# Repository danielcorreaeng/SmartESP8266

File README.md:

# SmartESP8266

Project for residential automation for ESP8266 NodeMcu board using arduino IDE with IR controller, MQTT and command line based HTTP request.

## Final note

I concluded that the best model is to use infrared with http and use a third program to manage the rest. 
In my case, I used the homeassistant (https://home-assistant.io/) and returned to the IR-Blaster model (https://github.com/mdhiggins/ESP8266-HTTP-IR-Blaster)

## Bases

https://github.com/mdhiggins/ESP8266-HTTP-IR-Blaster

https://github.com/tzapu/WiFiManager

https://www.filipeflop.com/blog/controle-monitoramento-iot-nodemcu-e-mqtt/

https://www.hackster.io/BuddyC/wifi-ir-blaster-af6bca

http://knolleary.net

## Contributors

See also the list of [contributors](contributors.md) who participated in this project.

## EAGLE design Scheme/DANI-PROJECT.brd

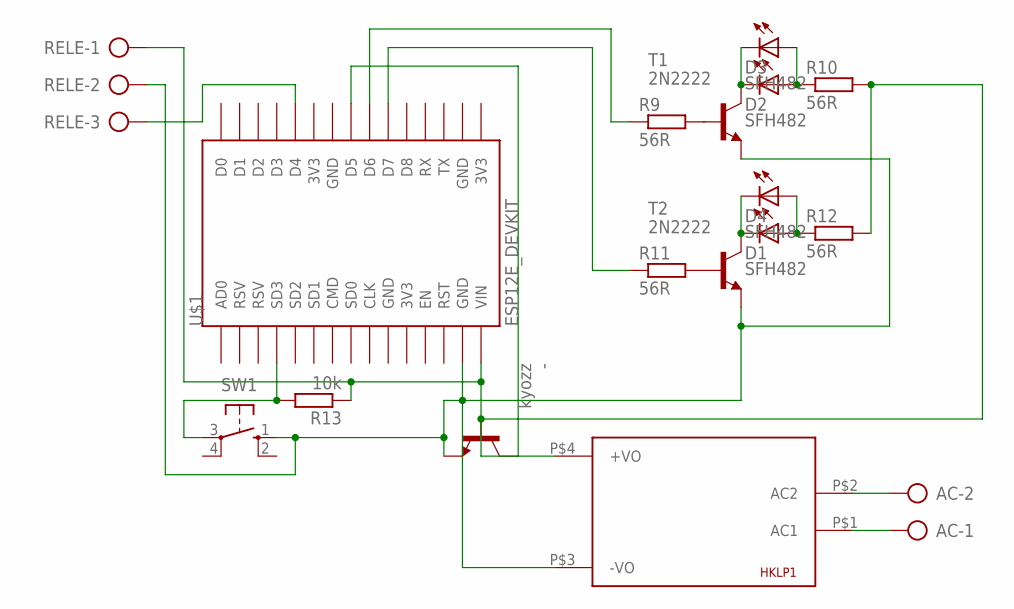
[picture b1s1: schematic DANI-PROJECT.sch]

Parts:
-: kyozz; TO92-EBC
AC: AK500/2-H
D1, D2, D3, D4: SFH482
HKLP1: HKLPM01
R9, R10, R11, R12: 56R; 0207/7
R13: 10k; 0207/7
RELE: AK500/3-H
SW1: 10-XX; B3F-10XX
T1, T2: 2N2222; TO18
U$1: ESP12E_DEVKIT

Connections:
unnamed: AC.2, HKLP1.P$2 (AC2)
unnamed: AC.1, HKLP1.P$1 (AC1)
unnamed: R13.2, SW1.3, U$1.SD3
unnamed: D1.K (C), D4.K (C), T2.3 (C)
unnamed: R11.2, T2.2 (B)
unnamed: R9.2, T1.2 (B)
unnamed: D2.A, D3.A, R10.1
unnamed: D2.K (C), D3.K (C), T1.3 (C)
unnamed: -.B, HKLP1.P$4 (+VO), R10.2, R12.2, R13.1, RELE.1, U$1.VIN
unnamed: D1.A, D4.A, R12.1
unnamed: R9.1, U$1.D6
unnamed: R11.1, U$1.D7
unnamed: -.E, HKLP1.P$3 (-VO), RELE.2, SW1.1 (S), T1.1 (E), T2.1 (E), U$1.GND@1 (GND)
unnamed: -.C, U$1.D5
unnamed: RELE.3, U$1.D4

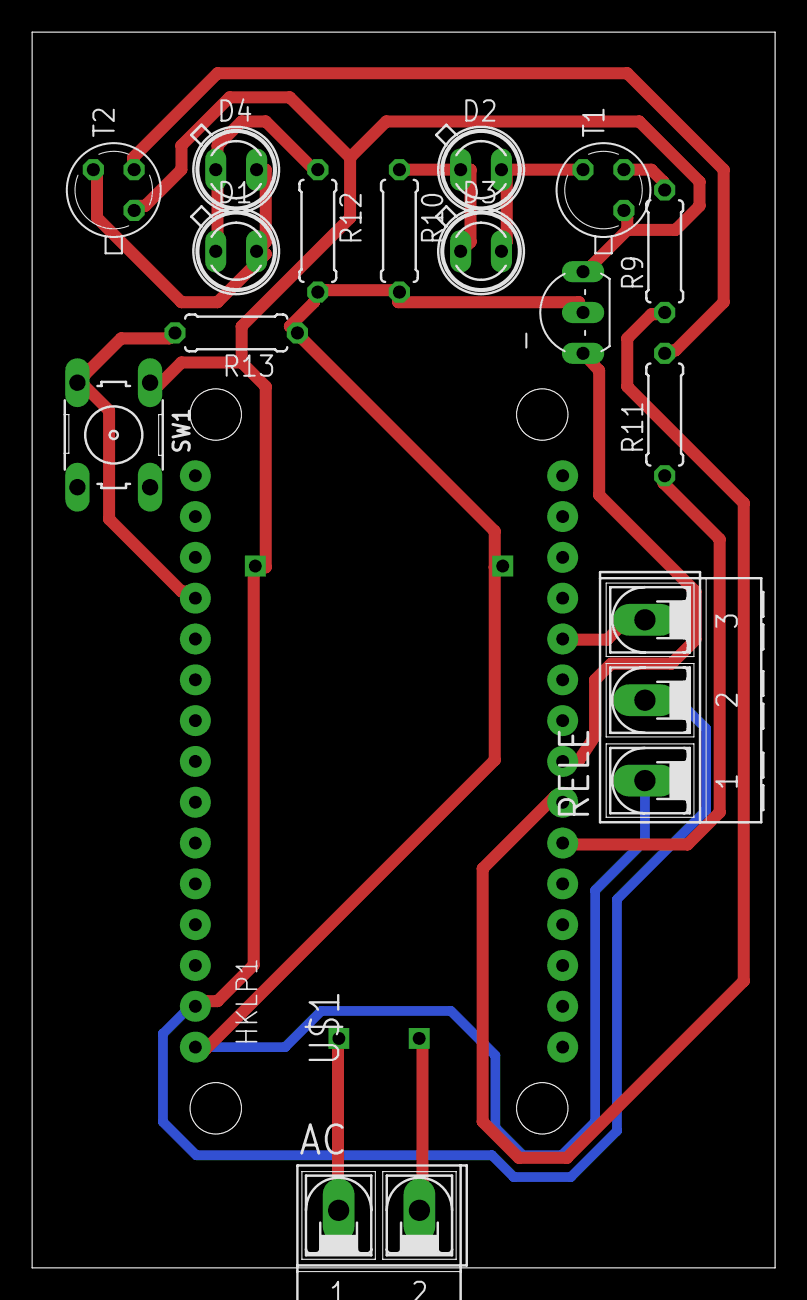
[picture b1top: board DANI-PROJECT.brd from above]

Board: 2 copper layers, 46.2 x 76.9 mm, 17 parts (0 on the bottom side), 15 nets.

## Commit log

2017-09-05 First commit with code base.
2017-11-09 upgrade version IRremoteESP8266 to version 2.2 https://github.com/markszabo/IRremoteESP8266
2017-11-09 After much development I conclude that the best model is to use infrared with http and use a third program to manage the rest.
    In my case, I use the homeassistant (https://home-assistant.io/) and returned to the IR-Blaster model (https://github.com/mdhiggins/ESP8266-HTTP-IR-Blaster)
2018-09-03 simplified circuit
2018-09-03 Update README.md
    Add notes
